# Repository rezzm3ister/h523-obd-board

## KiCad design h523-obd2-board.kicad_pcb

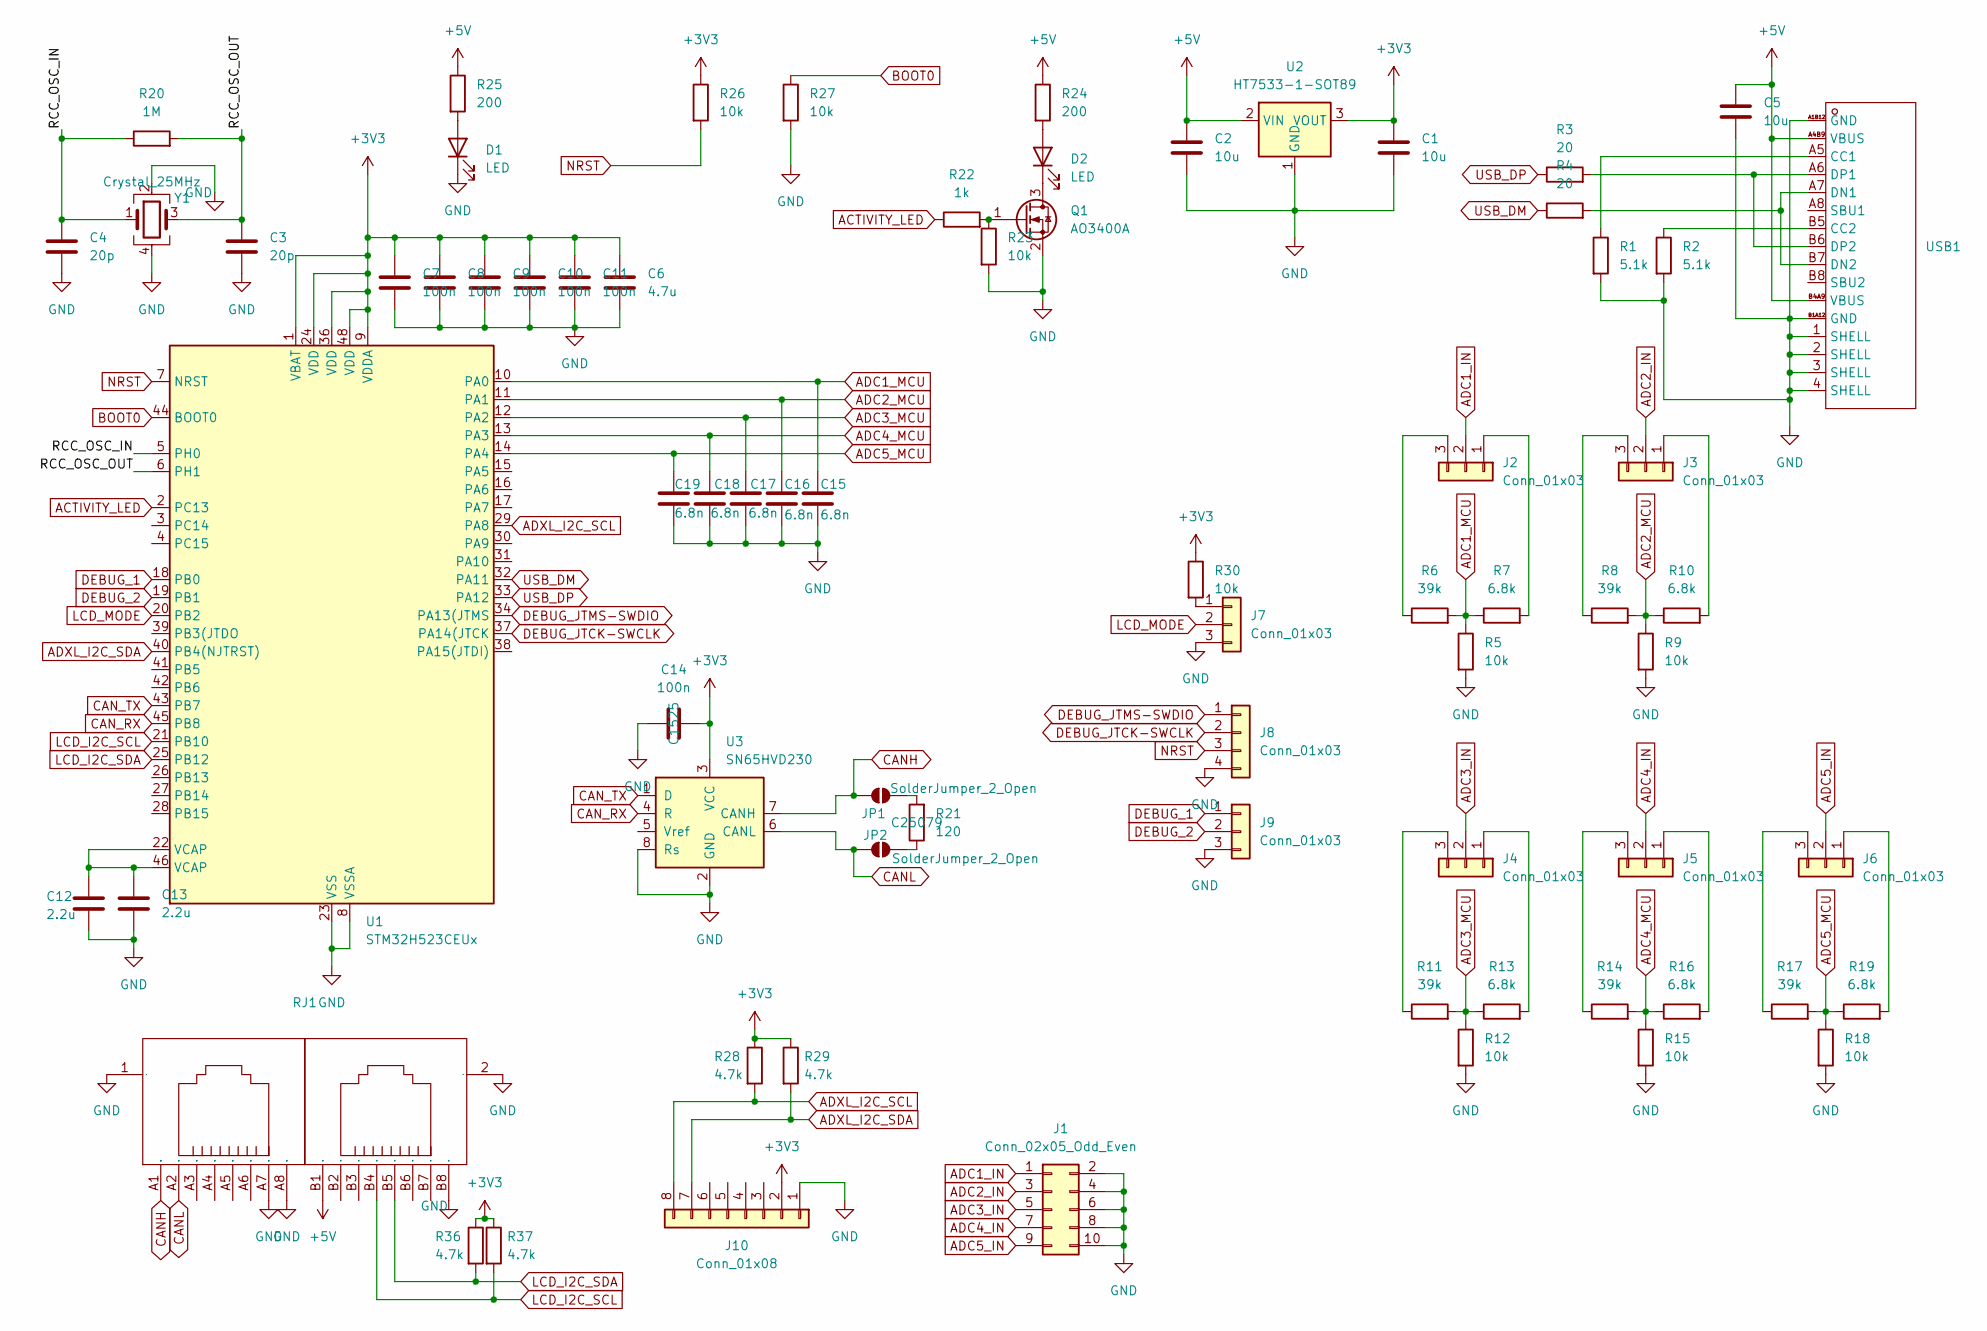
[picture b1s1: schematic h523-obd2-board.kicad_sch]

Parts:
C1, C2, C5: 10u; C_0603_1608Metric; LCSC C19702
C3, C4: 20p; C_0402_1005Metric; LCSC C1554
C6: 4.7u; C_0603_1608Metric; LCSC C19666
C7, C8, C9, C10, C11, C14: 100n; C_0402_1005Metric; LCSC C1525
C12, C13: 2.2u; C_0603_1608Metric; LCSC C23630
C15, C16, C17, C18, C19: 6.8n; C_0402_1005Metric; LCSC C1542
D1, D2: LED; LED_0603_1608Metric; LCSC C2286
J1: Conn_02x05_Odd_Even; PinHeader_2x05_P2.54mm_Horizontal
J2, J3, J4, J5, J6, J7, J9: Conn_01x03; PinHeader_1x03_P2.54mm_Vertical
J8: Conn_01x03; PinHeader_1x04_P2.54mm_Vertical
J10: Conn_01x08; PinHeader_1x08_P2.54mm_Vertical
JP1, JP2: SolderJumper_2_Open; SolderJumper-2_P1.3mm_Open_RoundedPad1.0x1.5mm
Q1: AO3400A; SOT-23; LCSC C20917
R1, R2: 5.1k; R_0402_1005Metric; LCSC C25905
R3, R4: 20; R_0603_1608Metric; LCSC C22950
R5, R9, R12, R15, R18, R23, R26, R27, R30: 10k; R_0402_1005Metric; LCSC C25744
R6, R8, R11, R14, R17: 39k; R_0402_1005Metric; LCSC C25783
R7, R10, R13, R16, R19: 6.8k; R_0402_1005Metric; LCSC C25917
R20: 1M; R_0402_1005Metric; LCSC C26083
R21: 120; R_0402_1005Metric; LCSC C25079
R22: 1k; R_0402_1005Metric; LCSC C11702
R24, R25: 200; R_0402_1005Metric; LCSC C25087
R28, R29, R36, R37: 4.7k; R_0402_1005Metric; LCSC C25900
RJ1: RJ45-TH_HC-WK88-H132-1X2-55B; Manufacturer Part HC-WK88-H132-1X2-55B; LCSC Part Name 弯插 不带LED 网口 RJ55双口半包 H=13.2 不锈钢壳
U1: STM32H523CEUx; QFN-48-1EP_7x7mm_P0.5mm_EP5.6x5.6mm
U2: HT7533-1-SOT89; SOT-89-3; LCSC C14289
U3: SN65HVD230; SOIC-8_3.9x4.9mm_P1.27mm; LCSC C12084
USB1: USB-C-SMD_TYPE-C16PIN; Manufacturer Part TYPE-C16PIN; LCSC Part Name Type-C 母 卧贴
Y1: Crystal_25MHz; Crystal_SMD_3225-4Pin_3.2x2.5mm; LCSC C9006

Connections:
+3V3: C1.1, C6.1, C7.1, C8.1, C9.1, C10.1, C11.1, C14.2, J10.2, R26.1, R28.1, R29.1, R30.1, R36.1, R37.1, U1.1 (VBAT), U1.9 (VDDA), U1.24 (VDD), U1.36 (VDD), U1.48 (VDD), U2.3 (VOUT), U3.3 (VCC)
+5V: C2.1, C5.1, R24.1, R25.1, RJ1.B1, U2.2 (VIN), USB1.A4B9 (VBUS), USB1.B4A9 (VBUS)
/RCC_OSC_IN: C4.1, R20.1, U1.5 (PH0), Y1.1
/RCC_OSC_OUT: C3.1, R20.2, U1.6 (PH1), Y1.3
ACTIVITY_LED: R22.1, U1.2 (PC13)
ADC1_IN: J1.1, J2.2
ADC1_MCU: C15.2, R5.1, R6.2, R7.1, U1.10 (PA0)
ADC2_IN: J1.3, J3.2
ADC2_MCU: C16.2, R8.2, R9.1, R10.1, U1.11 (PA1)
ADC3_IN: J1.5, J4.2
ADC3_MCU: C17.2, R11.2, R12.1, R13.1, U1.12 (PA2)
ADC4_IN: J1.7, J5.2
ADC4_MCU: C18.2, R14.2, R15.1, R16.1, U1.13 (PA3)
ADC5_IN: J1.9, J6.2
ADC5_MCU: C19.2, R17.2, R18.1, R19.1, U1.14 (PA4)
ADXL_I2C_SCL: J10.8, R28.2, U1.29 (PA8)
ADXL_I2C_SDA: J10.7, R29.2, U1.40 (PB4(NJTRST))
BOOT0: R27.1, U1.44 (BOOT0)
CANH: JP1.1 (A), RJ1.A1, U3.7 (CANH)
CANL: JP2.1 (A), RJ1.A2, U3.6 (CANL)
CAN_RX: U1.45 (PB8), U3.4 (R)
CAN_TX: U1.43 (PB7), U3.1 (D)
DEBUG_1: J9.1, U1.18 (PB0)
DEBUG_2: J9.2, U1.19 (PB1)
DEBUG_JTCK-SWCLK: J8.2, U1.37 (PA14(JTCK)
DEBUG_JTMS-SWDIO: J8.1, U1.34 (PA13(JTMS)
GND: C1.2, C2.2, C3.2, C4.2, C5.2, C6.2, C7.2, C8.2, C9.2, C10.2, C11.2, C12.2, C13.2, C14.1, C15.1, C16.1, C17.1, C18.1, C19.1, D1.1 (K), J1.2, J1.4, J1.6, J1.8, J1.10, J7.3, J8.4, J9.3, J10.1, Q1.2 (S), R1.2, R2.2, R5.2, R9.2, R12.2, R15.2, R18.2, R23.2, R27.2, RJ1.1, RJ1.2, RJ1.A7, RJ1.A8, RJ1.B8, U1.8 (VSSA), U1.23 (VSS), U1.35 (VSS), U1.47 (VSS), U1.49 (VSS), U2.1 (GND), U3.2 (GND), U3.8 (Rs), USB1.1 (SHELL), USB1.2 (SHELL), USB1.3 (SHELL), USB1.4 (SHELL), USB1.A1B12 (GND), USB1.B1A12 (GND), Y1.2, Y1.4
LCD_I2C_SCL: R37.2, RJ1.B4, U1.21 (PB10)
LCD_I2C_SDA: R36.2, RJ1.B5, U1.25 (PB12)
LCD_MODE: J7.2, U1.20 (PB2)
NRST: J8.3, R26.2, U1.7 (NRST)
unnamed: C12.1, C13.1, U1.22 (VCAP), U1.46 (VCAP)
unnamed: D1.2 (A), R25.2
unnamed: D2.2 (A), R24.2
unnamed: D2.1 (K), Q1.3 (D)
unnamed: J2.1, R7.2
unnamed: J2.3, R6.1
unnamed: J3.1, R10.2
unnamed: J3.3, R8.1
unnamed: J4.1, R13.2
unnamed: J4.3, R11.1
unnamed: J5.1, R16.2
unnamed: J5.3, R14.1
unnamed: J6.1, R19.2
unnamed: J6.3, R17.1
unnamed: J7.1, R30.2
unnamed: JP1.2 (B), R21.2
unnamed: JP2.2 (B), R21.1
unnamed: Q1.1 (G), R22.2, R23.1
unnamed: R1.1, USB1.A5 (CC1)
unnamed: R2.1, USB1.B5 (CC2)
unnamed: R4.2, USB1.A7 (DN1), USB1.B7 (DN2)
unnamed: R3.2, USB1.A6 (DP1), USB1.B6 (DP2)
USB_DM: R4.1, U1.32 (PA11)
USB_DP: R3.1, U1.33 (PA12)

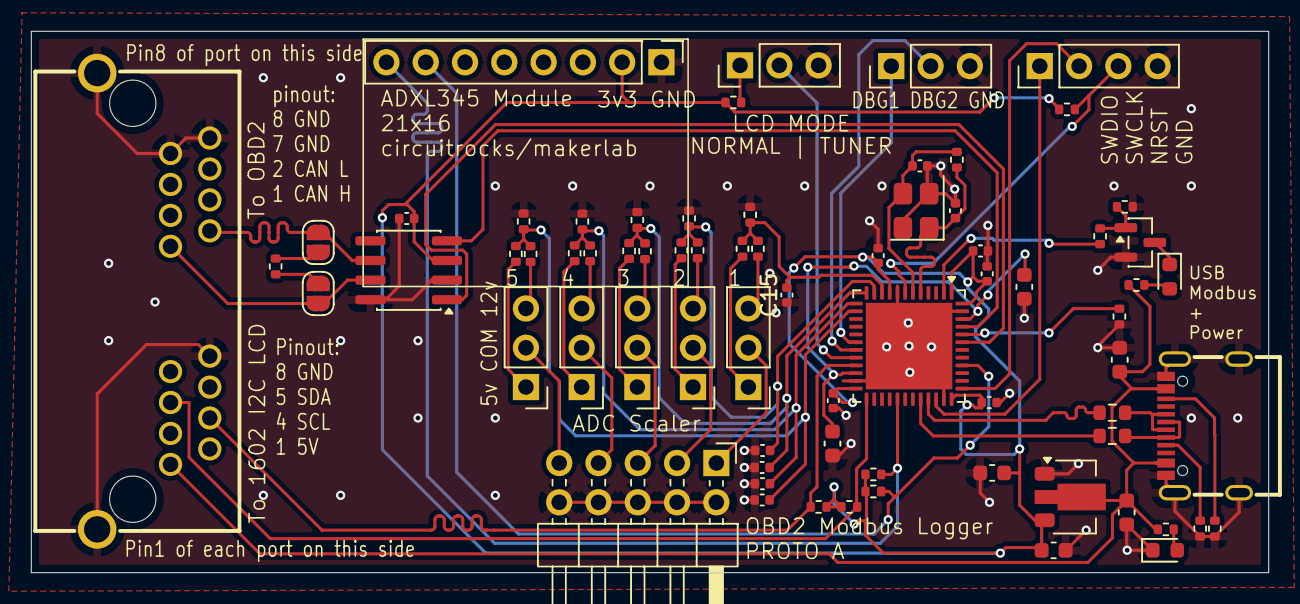
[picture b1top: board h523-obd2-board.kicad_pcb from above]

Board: 2 copper layers, 80.0 x 35.0 mm, 72 parts (0 on the bottom side), 55 nets.

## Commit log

2026-06-21 finished proto A
2026-06-21 updated BOM for supporting parts
2026-06-29 PROTO A manufactured
